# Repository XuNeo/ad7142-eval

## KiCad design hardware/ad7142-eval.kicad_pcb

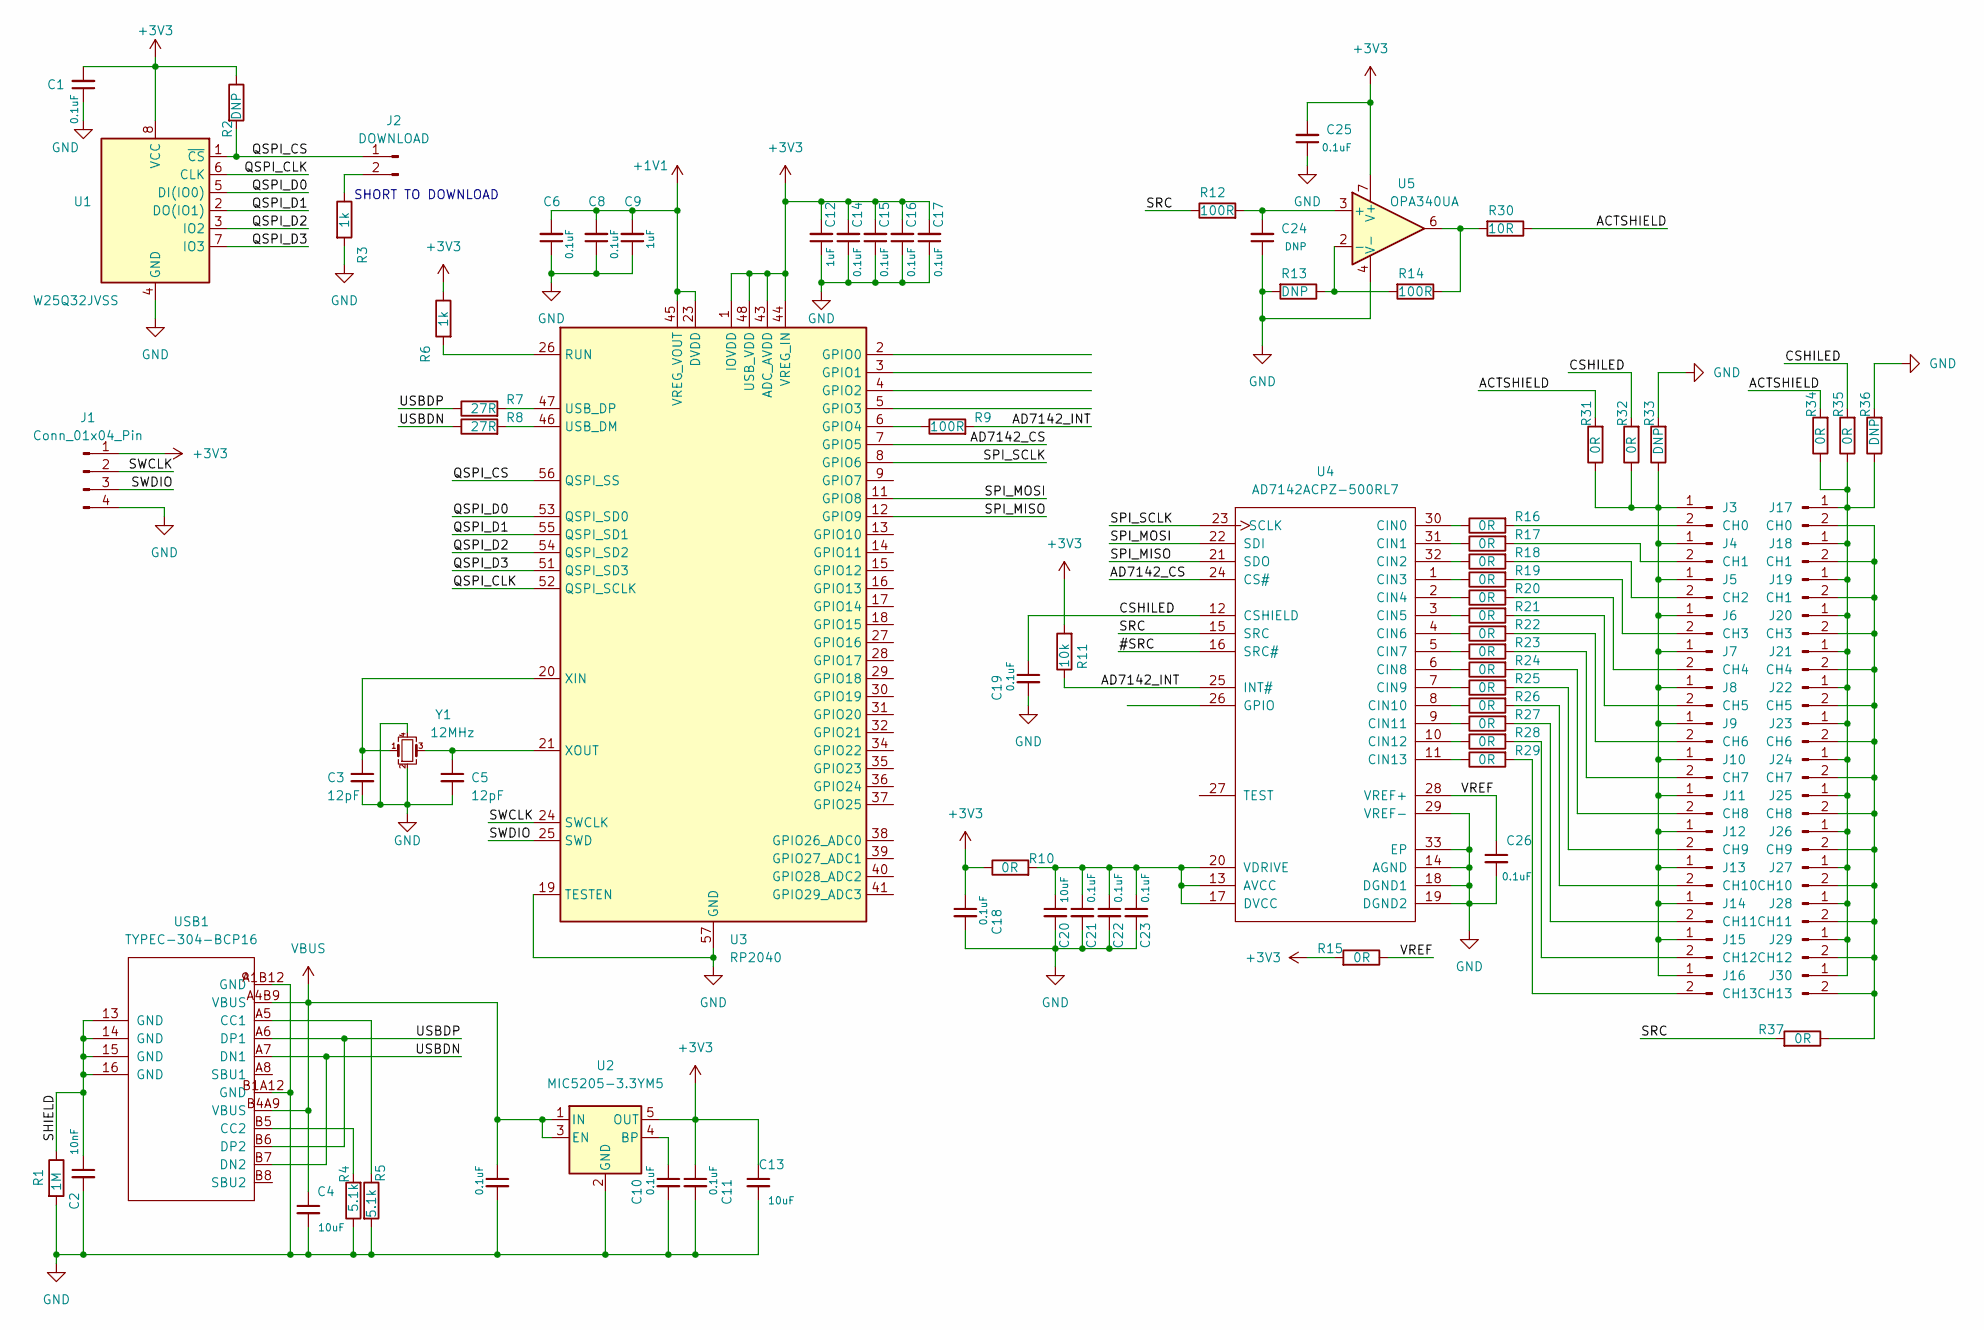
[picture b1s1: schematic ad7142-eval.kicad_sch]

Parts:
C1, C6, C7, C8, C10, C11, C14, C15, C16, C17, C18, C19, C21, C22, C23, C25, C26: 0.1uF; C_0402_1005Metric_Pad0.74x0.62mm_HandSolder
C2: 10nF; C_0402_1005Metric_Pad0.74x0.62mm_HandSolder
C3, C5: 12pF; C_0402_1005Metric_Pad0.74x0.62mm_HandSolder
C4, C13, C20: 10uF; C_0402_1005Metric_Pad0.74x0.62mm_HandSolder
C9, C12: 1uF; C_0402_1005Metric_Pad0.74x0.62mm_HandSolder
C24: DNP; C_0402_1005Metric_Pad0.74x0.62mm_HandSolder
J1: Conn_01x04_Pin; PinHeader_1x04_P2.54mm_Vertical
J2: DOWNLOAD; PinHeader_1x02_P2.54mm_Vertical
J3, J17: CH0; PinHeader_1x02_P2.00mm_Vertical
J4, J18, J19: CH1; PinHeader_1x02_P2.00mm_Vertical
J5: CH2; PinHeader_1x02_P2.00mm_Vertical
J6, J20: CH3; PinHeader_1x02_P2.00mm_Vertical
J7, J21: CH4; PinHeader_1x02_P2.00mm_Vertical
J8, J22: CH5; PinHeader_1x02_P2.00mm_Vertical
J9, J23: CH6; PinHeader_1x02_P2.00mm_Vertical
J10, J24: CH7; PinHeader_1x02_P2.00mm_Vertical
J11, J25: CH8; PinHeader_1x02_P2.00mm_Vertical
J12, J26: CH9; PinHeader_1x02_P2.00mm_Vertical
J13, J27: CH10; PinHeader_1x02_P2.00mm_Vertical
J14, J28: CH11; PinHeader_1x02_P2.00mm_Vertical
J15, J29: CH12; PinHeader_1x02_P2.00mm_Vertical
J16, J30: CH13; PinHeader_1x02_P2.00mm_Vertical
R1: 1M; R_0402_1005Metric_Pad0.72x0.64mm_HandSolder
R2, R13, R33, R36: DNP; R_0402_1005Metric_Pad0.72x0.64mm_HandSolder
R3, R6: 1k; R_0402_1005Metric_Pad0.72x0.64mm_HandSolder
R4, R5: 5.1k; R_0402_1005Metric_Pad0.72x0.64mm_HandSolder
R7, R8: 27R; R_0402_1005Metric_Pad0.72x0.64mm_HandSolder
R9, R12, R14: 100R; R_0402_1005Metric_Pad0.72x0.64mm_HandSolder
R10, R15, R16, R17, R18, R19, R20, R21, R22, R23, R24, R25, R26, R27, R28, R29, R31, R32, R34, R35, R37: 0R; R_0402_1005Metric_Pad0.72x0.64mm_HandSolder
R11: 10k; R_0402_1005Metric_Pad0.72x0.64mm_HandSolder
R30: 10R; R_0402_1005Metric_Pad0.72x0.64mm_HandSolder
U1: W25Q32JVSS; SOIC-8_5.23x5.23mm_P1.27mm
U2: MIC5205-3.3YM5; SOT-23-5
U3: RP2040; QFN-56-1EP_7x7mm_P0.4mm_EP3.2x3.2mm
U4: AD7142ACPZ-500RL7; LFCSP-32-1EP_5x5mm_P0.5mm_EP3.1x3.1mm
U5: OPA340UA; SOIC-8_3.9x4.9mm_P1.27mm
USB1: TYPEC-304-BCP16; USB-C-SMD_TYPEC-304-BCP16
Y1: 12MHz; Crystal_SMD_SeikoEpson_FA238-4Pin_3.2x2.5mm

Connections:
+1V1: C6.2, C8.2, C9.2, U3.23 (DVDD), U3.45 (VREG_VOUT), U3.50 (DVDD)
+3V3: C1.2, C11.1, C12.2, C13.1, C14.2, C15.2, C16.2, C17.2, C18.1, C25.2, J1.1, R2.1, R6.1, R10.1, R11.2, R15.2, U1.8 (VCC), U2.5 (OUT), U3.1 (IOVDD), U3.10 (IOVDD), U3.22 (IOVDD), U3.33 (IOVDD), U3.42 (IOVDD), U3.43 (ADC_AVDD), U3.44 (VREG_IN), U3.48 (USB_VDD), U3.49 (IOVDD), U5.7 (V+)
/#SRC: U4.16 (SRC#)
/ACTSHIELD: R30.1, R31.2, R34.2
/AD7142_CS: U3.7 (GPIO5), U4.24 (CS#)
/AD7142_INT: R9.2, R11.1, U4.25 (INT#)
/CSHILED: C19.1, R32.2, R35.2, U4.12 (CSHIELD)
/QSPI_CLK: U1.6 (CLK), U3.52 (QSPI_SCLK)
/QSPI_CS: J2.1, R2.2, U1.1 (~CS), U3.56 (QSPI_SS)
/QSPI_D0: U1.5 (DI(IO0)), U3.53 (QSPI_SD0)
/QSPI_D1: U1.2 (DO(IO1)), U3.55 (QSPI_SD1)
/QSPI_D2: U1.3 (IO2), U3.54 (QSPI_SD2)
/QSPI_D3: U1.7 (IO3), U3.51 (QSPI_SD3)
/SHIELD: C2.1, R1.1, USB1.13 (GND), USB1.14 (GND), USB1.15 (GND), USB1.16 (GND)
/SPI_MISO: U3.12 (GPIO9), U4.21 (SDO)
/SPI_MOSI: U3.11 (GPIO8), U4.22 (SDI)
/SPI_SCLK: U3.8 (GPIO6), U4.23 (SCLK)
/SRC: R12.1, R37.2, U4.15 (SRC)
/SWCLK: J1.2, U3.24 (SWCLK)
/SWDIO: J1.3, U3.25 (SWD)
/USBDN: R8.1, USB1.A7 (DN1), USB1.B7 (DN2)
/USBDP: R7.1, USB1.A6 (DP1), USB1.B6 (DP2)
/VREF: C26.1, R15.1, U4.28 (VREF+)
GND: C1.1, C2.2, C3.2, C4.2, C5.2, C6.1, C7.2, C8.1, C9.1, C10.2, C11.2, C12.1, C13.2, C14.1, C15.1, C16.1, C17.1, C18.2, C19.2, C20.2, C21.2, C22.2, C23.2, C24.1, C25.1, C26.2, J1.4, R1.2, R3.2, R4.1, R5.2, R13.2, R33.2, R36.2, U1.4 (GND), U2.2 (GND), U3.19 (TESTEN), U3.57 (GND), U4.14 (AGND), U4.18 (DGND1), U4.19 (DGND2), U4.29 (VREF-), U4.33 (EP), U5.4 (V-), USB1.A1B12 (GND), USB1.B1A12 (GND), Y1.2, Y1.4
unnamed: J2.2, R3.1
unnamed: J3.2, R16.2
unnamed: J4.2, R17.2
unnamed: J5.2, R18.2
unnamed: J6.2, R19.2
unnamed: J7.2, R20.2
unnamed: J8.2, R21.2
unnamed: J9.2, R22.2
unnamed: J3.1, J4.1, J5.1, J6.1, J7.1, J8.1, J9.1, J10.1, J11.1, J12.1, J13.1, J14.1, J15.1, J16.1, R31.1, R32.1, R33.1
unnamed: J10.2, R23.2
unnamed: J11.2, R24.2
unnamed: J12.2, R25.2
unnamed: J13.2, R26.2
unnamed: J14.2, R27.2
unnamed: J15.2, R28.2
unnamed: J16.2, R29.2
unnamed: J17.1, J18.1, J19.1, J20.1, J21.1, J22.1, J23.1, J24.1, J25.1, J26.1, J27.1, J28.1, J29.1, J30.1, R34.1, R35.1, R36.1
unnamed: J17.2, J18.2, J19.2, J20.2, J21.2, J22.2, J23.2, J24.2, J25.2, J26.2, J27.2, J28.2, J29.2, J30.2, R37.1
unnamed: R14.1, R30.2, U5.6
unnamed: C10.1, U2.4 (BP)
unnamed: R9.1, U3.6 (GPIO4)
unnamed: R6.2, U3.26 (RUN)
unnamed: R8.2, U3.46 (USB_DM)
unnamed: R7.2, U3.47 (USB_DP)
unnamed: C3.1, U3.20 (XIN), Y1.1
unnamed: C5.1, U3.21 (XOUT), Y1.3
unnamed: C20.1, C21.1, C22.1, C23.1, R10.2, U4.13 (AVCC), U4.17 (DVCC), U4.20 (VDRIVE)
unnamed: R16.1, U4.30 (CIN0)
unnamed: R17.1, U4.31 (CIN1)
unnamed: R18.1, U4.32 (CIN2)
unnamed: R19.1, U4.1 (CIN3)
unnamed: R20.1, U4.2 (CIN4)
unnamed: R21.1, U4.3 (CIN5)
unnamed: R22.1, U4.4 (CIN6)
unnamed: R23.1, U4.5 (CIN7)
unnamed: R24.1, U4.6 (CIN8)
unnamed: R25.1, U4.7 (CIN9)
unnamed: R26.1, U4.8 (CIN10)
unnamed: R27.1, U4.9 (CIN11)
unnamed: R28.1, U4.10 (CIN12)
unnamed: R29.1, U4.11 (CIN13)
unnamed: C24.2, R12.2, U5.3 (+)
unnamed: R13.1, R14.2, U5.2 (-)
unnamed: R5.1, USB1.A5 (CC1)
unnamed: R4.2, USB1.B5 (CC2)
VBUS: C4.1, C7.1, U2.1 (IN), U2.3 (EN), USB1.A4B9 (VBUS), USB1.B4A9 (VBUS)

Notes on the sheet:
SHORT TO DOWNLOAD

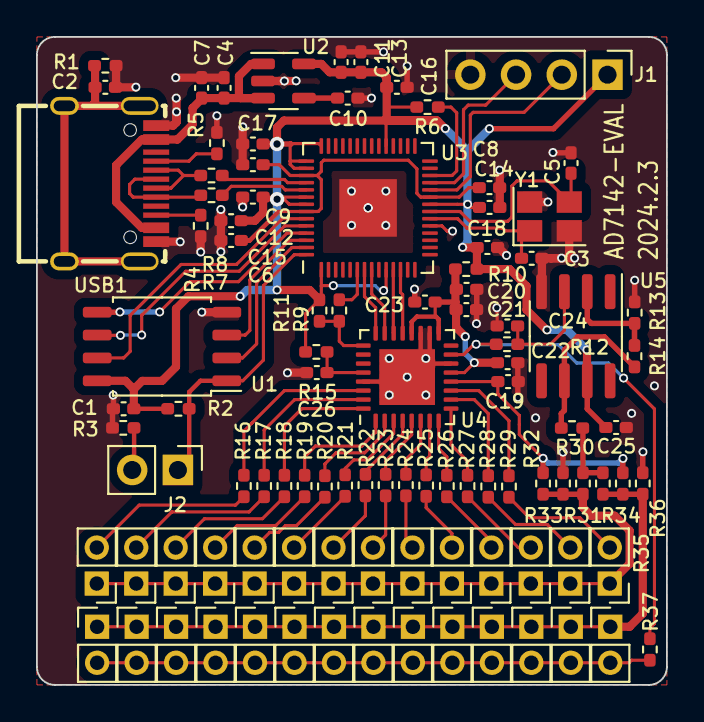
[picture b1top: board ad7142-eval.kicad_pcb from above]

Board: 2 copper layers, 35.0 x 36.0 mm, 100 parts (0 on the bottom side), 69 nets.

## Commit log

2024-03-04 ad7142-eval: add initial pcb and sch
